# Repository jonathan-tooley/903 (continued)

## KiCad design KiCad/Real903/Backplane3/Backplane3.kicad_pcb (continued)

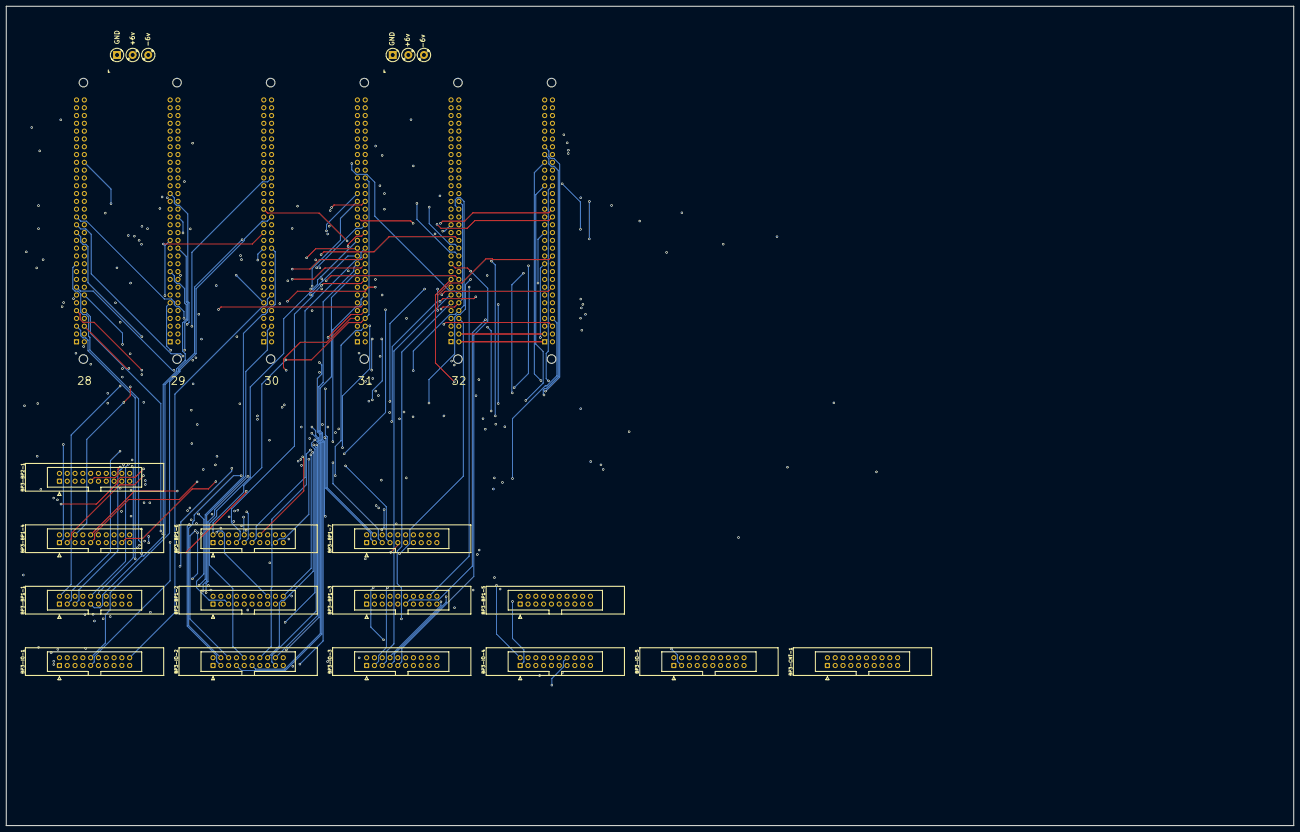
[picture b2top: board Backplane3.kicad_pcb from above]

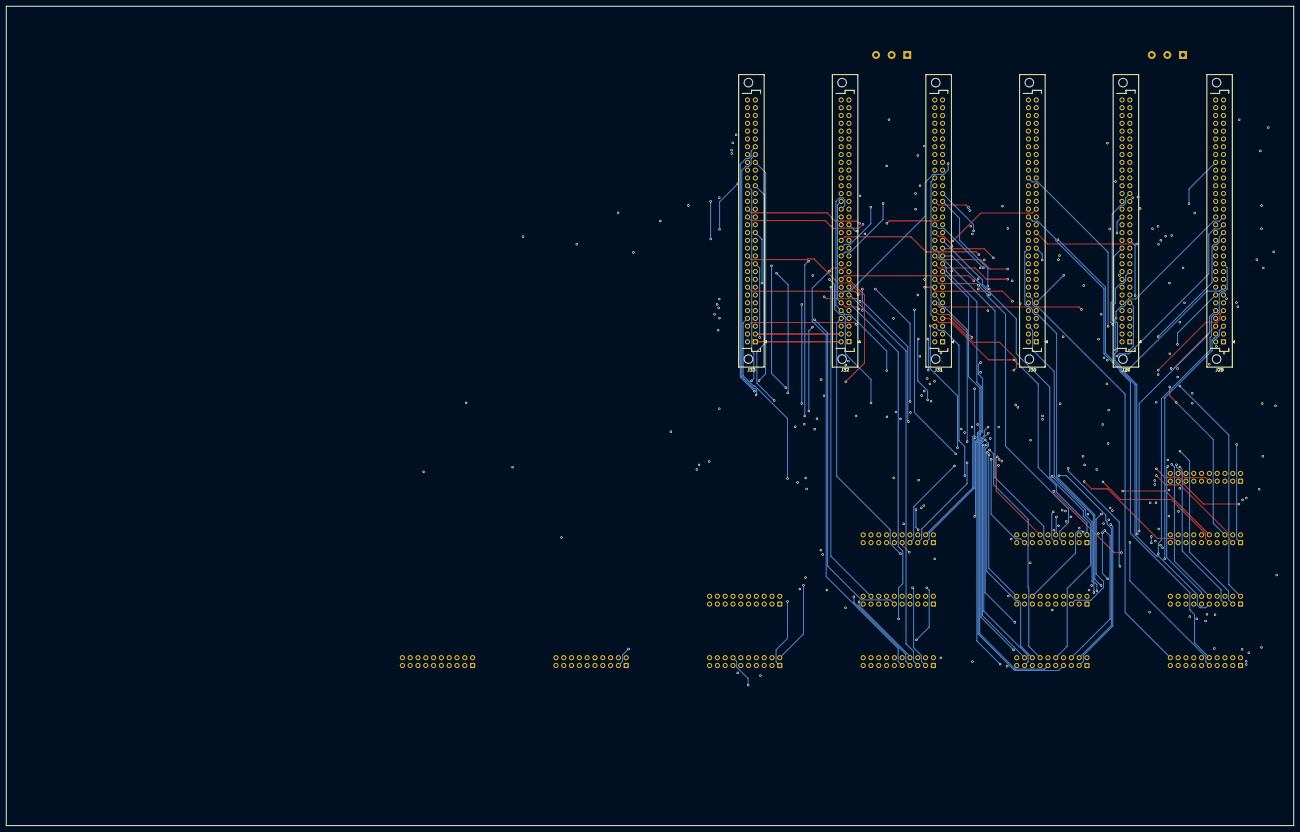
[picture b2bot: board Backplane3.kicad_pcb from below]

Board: 4 copper layers, 419.1 x 266.7 mm, 22 parts (6 on the bottom side), 236 nets.

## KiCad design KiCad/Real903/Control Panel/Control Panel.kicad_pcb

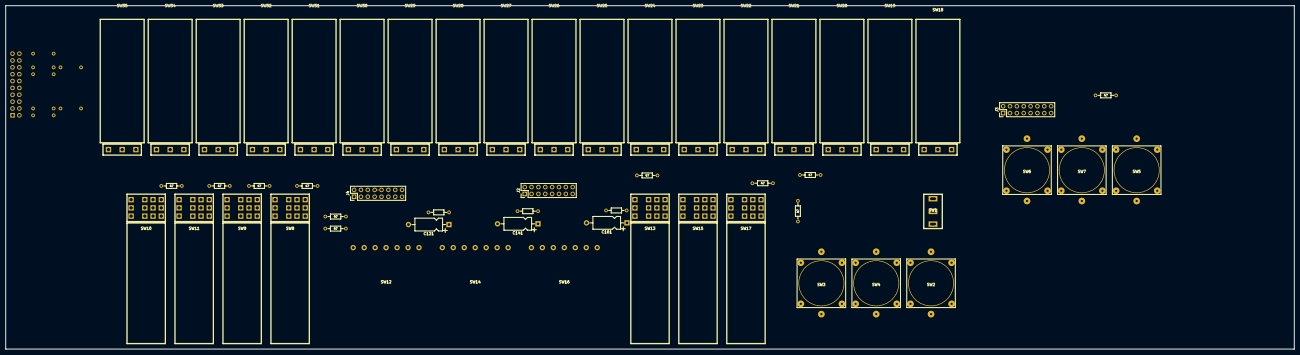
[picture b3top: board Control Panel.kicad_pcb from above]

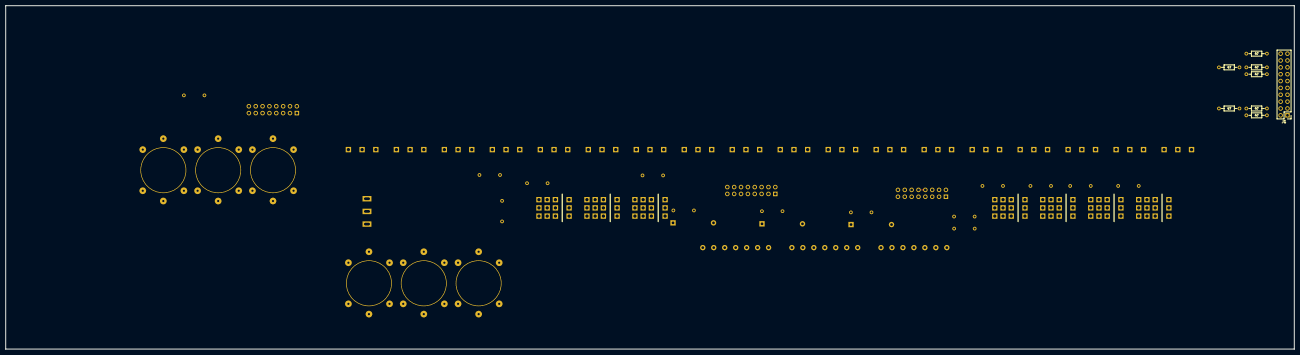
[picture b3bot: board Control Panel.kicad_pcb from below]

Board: 2 copper layers, 477.5 x 127.3 mm, 63 parts (8 on the bottom side), 92 nets.

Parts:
C121, C141, C161: CP_Axial_L10.0mm_D4.5mm_P15.00mm_Horizontal
J1: PinHeader_2x10_P2.54mm_Vertical
J2, J3, J4: PinHeader_2x08_P2.54mm_Vertical
R19, R20, R21, R24, R25, R29, R30, R31, R32, R33, R34, R35, R37, R38, R39, R40, R41, R42: 47; R_Axial_DIN0204_L3.6mm_D1.6mm_P7.62mm_Horizontal
R121, R141, R161: R_Axial_DIN0204_L3.6mm_D1.6mm_P7.62mm_Horizontal
SW1: MiniSPDTSwitch
SW2: Jump; EAO31
SW3: Stop; EAO31
SW4: Restart; EAO31
SW5: Reset; EAO31
SW6: On; EAO31
SW7: Off; EAO31
SW8: Obey; ElliottCPSwitch
SW9: Enter; ElliottCPSwitch
SW10: O/C Stop; ElliottCPSwitch
SW11: Cycle Repeat; ElliottCPSwitch
SW12: Int1; Honeywell Sw
SW13, SW15, SW17: Man/Trace; ElliottCPSwitch
SW14: Int2; Honeywell Sw
SW16: Int3; Honeywell Sw
SW18: NG1; ElliottNGSwitch
SW19: NG2; ElliottNGSwitch
SW20: NG3; ElliottNGSwitch
SW21: NG4; ElliottNGSwitch
SW22: NG5; ElliottNGSwitch
SW23: NG6; ElliottNGSwitch
SW24: NG7; ElliottNGSwitch
SW25: NG8; ElliottNGSwitch
SW26: NG9; ElliottNGSwitch
SW27: NG10; ElliottNGSwitch
SW28: NG11; ElliottNGSwitch
SW29: NG12; ElliottNGSwitch
SW30: NG13; ElliottNGSwitch
SW31: NG14; ElliottNGSwitch
SW32: NG15; ElliottNGSwitch
SW33: NG16; ElliottNGSwitch
SW34: NG17; ElliottNGSwitch
SW35: NG18; ElliottNGSwitch

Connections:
0v: J3.13, SW1.3, SW2.1, SW5.2, SW6.4, SW13.4, SW15.4, SW17.4
+6va: J3.16, R19.1, R20.1, R21.1, SW6.5, SW12.3, SW12.7, SW13.6, SW14.3, SW14.7, SW15.6, SW16.3, SW16.7, SW17.6
+6vb: J3.15, SW3.5, SW5.5, SW12.5, SW14.5, SW16.5
A: J3.8, SW1.2
CINS: J4.4, SW9.8
ENGk: J4.8, R42.1
INT1a: J2.14, SW13.5
INT1b: J2.16, R121.1
INT2a: J2.10, SW15.5
INT2b: J2.12, R141.1
INT3a: J2.6, SW17.5
INT3b: J2.8, R161.1
L: J3.14, SW7.5
M: J3.11, SW7.4
NG-1k: J3.1, SW18.1
NG-5k: J1.2, SW22.1
NG-6k: J1.3, SW23.1
NG-7k: J1.4, SW24.1
NG-8k: J1.5, SW25.1
NG-9k: J1.6, SW26.1
NG-10k: J1.7, SW27.1
NG-11k: J1.8, SW28.1
NG-12k: J1.9, SW29.1
NG-13k: J1.10, SW30.1
NG-17: J1.14, SW34.1
unnamed: C121.1, R121.2
unnamed: C121.2, SW12.2
unnamed: C141.1, R141.2
unnamed: C141.2, SW14.2
unnamed: C161.1, R161.2
unnamed: C161.2, SW16.2
unnamed: R19.2, SW13.1
unnamed: R20.2, SW15.1
unnamed: R21.2, SW17.1
unnamed: R24.2, SW3.3
unnamed: R25.2, SW5.1
unnamed: R29.2, SW35.3
unnamed: R30.2, SW33.3
unnamed: R31.2, SW32.3
unnamed: R32.2, SW31.3
unnamed: R33.2, SW21.3
unnamed: R34.2, SW20.3
unnamed: R35.2, SW19.3
unnamed: R37.2, SW8.4
unnamed: R38.2, SW8.3, SW8.6
unnamed: R39.2, SW10.3
unnamed: R40.2, SW11.3
unnamed: R41.2, SW9.3, SW9.6
unnamed: R42.2, SW9.4
unnamed: SW8.1, SW8.5
unnamed: SW8.7, SW9.7, SW9.12
unnamed: SW8.9, SW9.10
unnamed: SW9.1, SW9.5
unnamed: SW10.1, SW10.5
ONGk: J4.12, R37.1
ONOFFCommon: J3.7, SW7.2
Off: J3.9, SW6.2, SW7.1
On: J3.12, SW6.3
RESET: J3.6, SW5.4
RESETk: J3.4, R25.1
RSTk: J2.1, SW4.1
STOP: J2.5, SW3.4
{ACTIVE1}: J4.7, SW12.6
{ACTIVE2}: J4.3, SW14.6
{ACTIVE3}: J2.15, SW16.6
{INT1}: J4.5, SW12.4
{INT2}: J4.1, SW14.4
{INT3}: J2.13, SW16.4
~CINS: J4.2, SW9.11
~CSk: J4.15, SW10.6
~ENGk: J4.6, R41.1
~JUMP: J2.4, SW2.2
~NG-2k: J3.2, R35.1
~NG-3k: J3.3, R34.1
~NG-4k: J1.1, R33.1
~NG-14k: J1.11, R32.1
~NG-15k: J1.12, R31.1
~NG-16k: J1.13, R30.1
~NG-17: J1.15, SW34.3
~NG-18k: J1.16, R29.1
~ONGk: J4.10, R38.1
~OSk: J4.11, R39.1
~Operate: SW3.2, SW4.2, SW13.3, SW15.3, SW17.3, SW18.2, SW19.2, SW20.2, SW21.2, SW22.2, SW23.2, SW24.2, SW25.2, SW26.2, SW27.2, SW28.2, SW29.2, SW30.2
~PS1: J2.11, SW12.1, SW13.2
~PS2: J2.9, SW14.1, SW15.2
~PS3: J2.7, SW16.1, SW17.2
~RSTk: J2.2, SW4.3
~SMNk: J4.13, SW10.4
~STOPk: J2.3, R24.1
~TCSk: J4.9, R40.1
~TEST: SW8.2, SW8.8, SW9.2, SW10.2, SW11.2
~TestNoJump: J3.5, SW31.2, SW32.2, SW33.2, SW34.2, SW35.2

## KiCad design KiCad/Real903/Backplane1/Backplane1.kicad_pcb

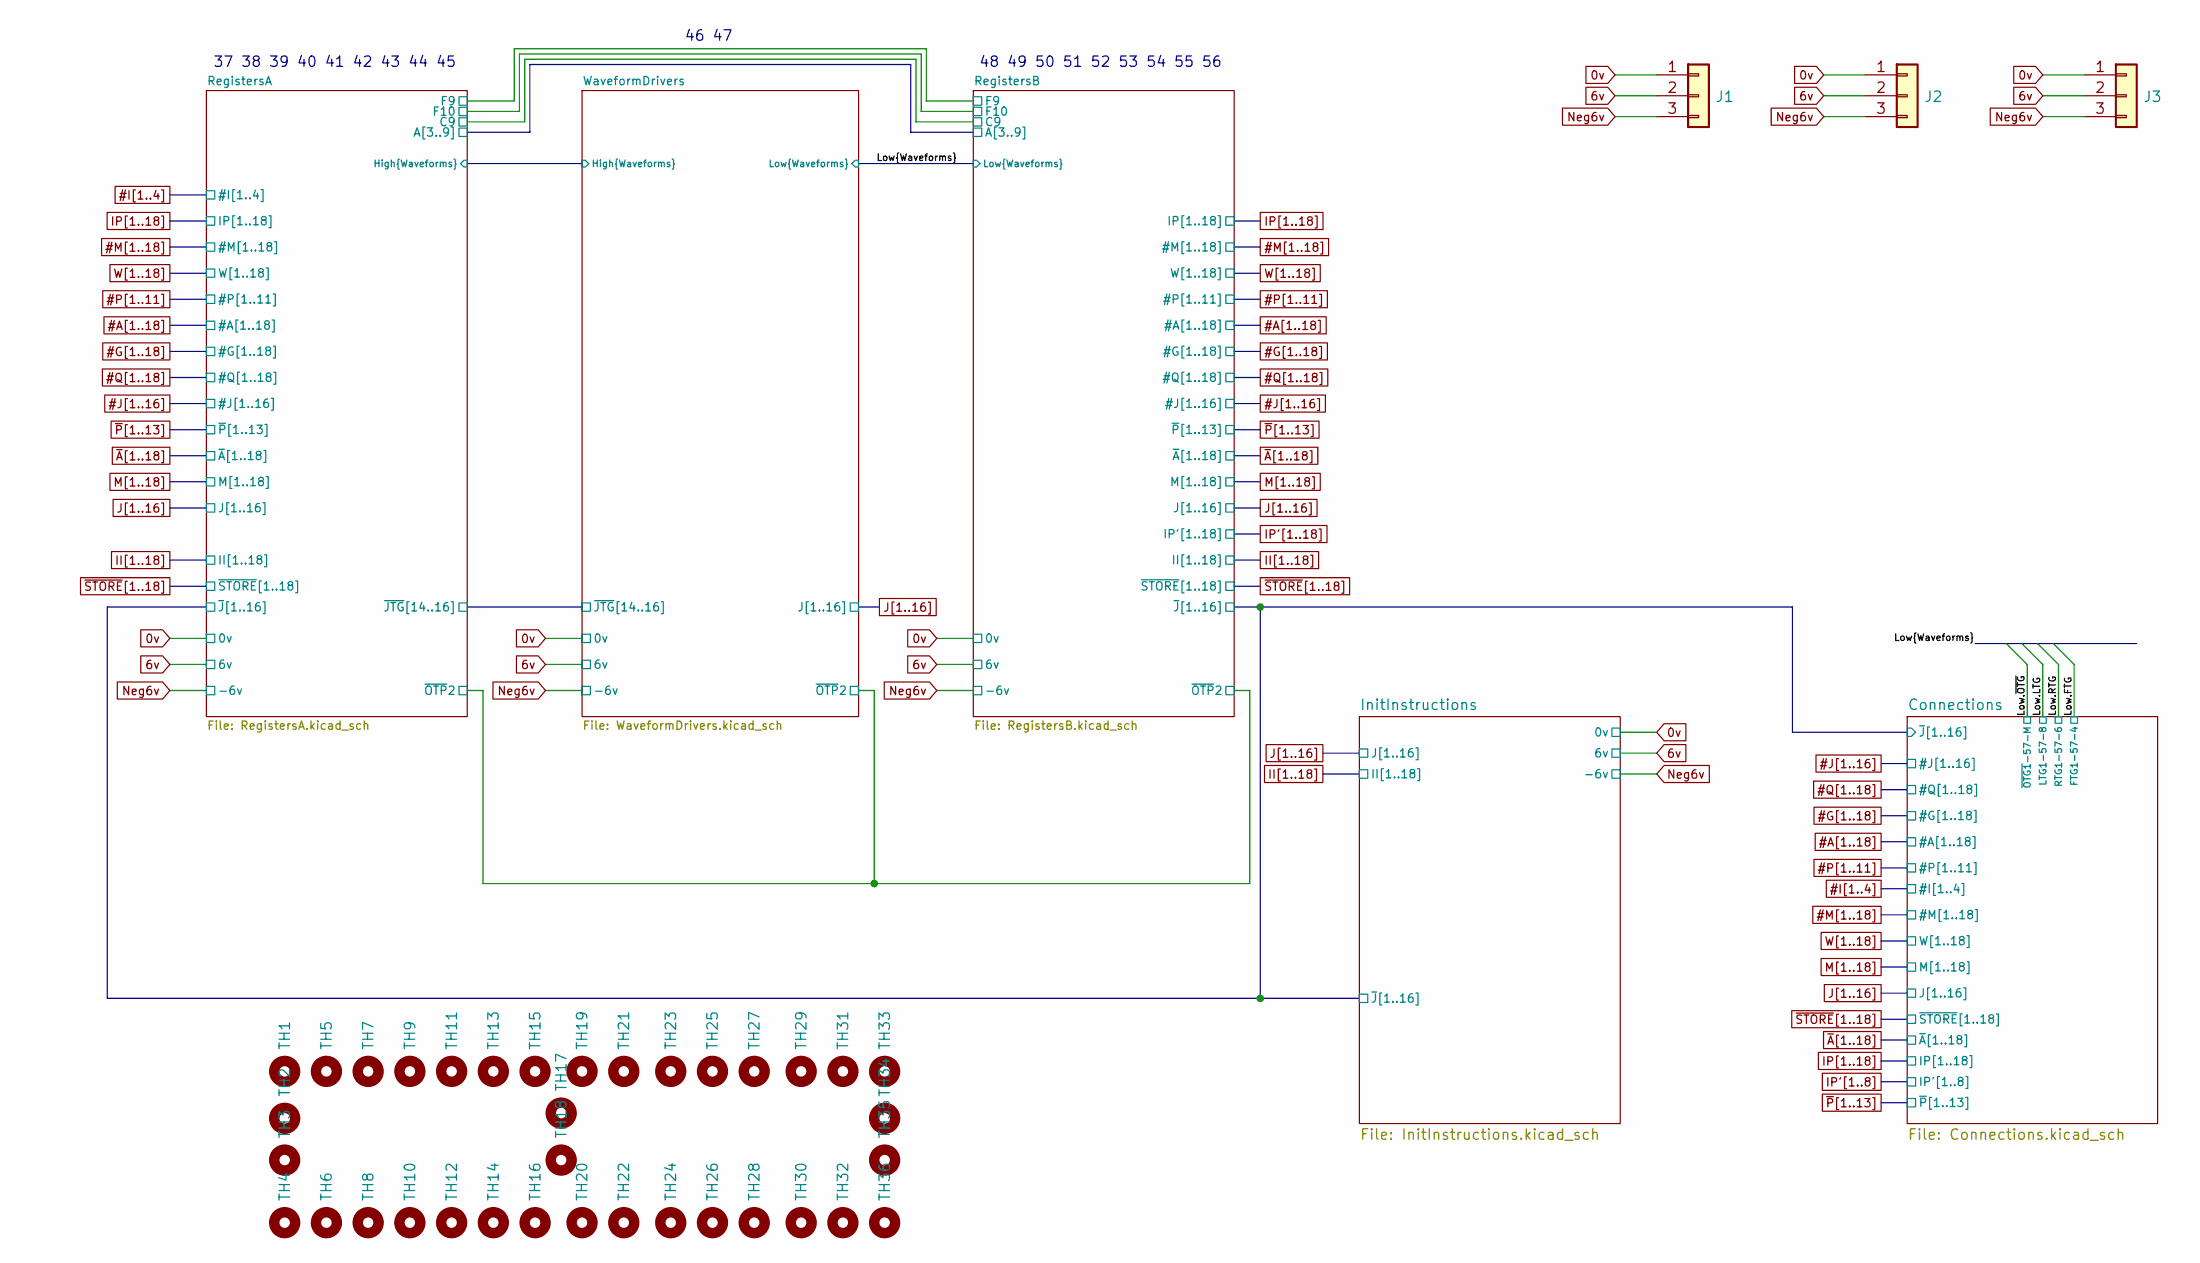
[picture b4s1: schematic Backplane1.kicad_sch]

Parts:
J1, J2, J3: TerminalBlock_5.08_1x03
TH1, TH2, TH3, TH4, TH5, TH6, TH7, TH8, TH9, TH10, TH11, TH12, TH13, TH14, TH15, TH16, TH17, TH18, TH19, TH20, TH21, TH22, TH23, TH24, TH25, TH26, TH27, TH28, TH29, TH30, TH31, TH32, TH33, TH34, TH35, TH36: MountingHole_2.7mm

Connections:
0v: J1.1, J2.1, J3.1; also elsewhere on the board
6v: J1.2, J2.2, J3.2; also elsewhere on the board
Neg6v: J1.3, J2.3, J3.3; also elsewhere on the board

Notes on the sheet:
48 49 50 51 52 53 54 55 56
37 38 39 40 41 42 43 44 45
46 47

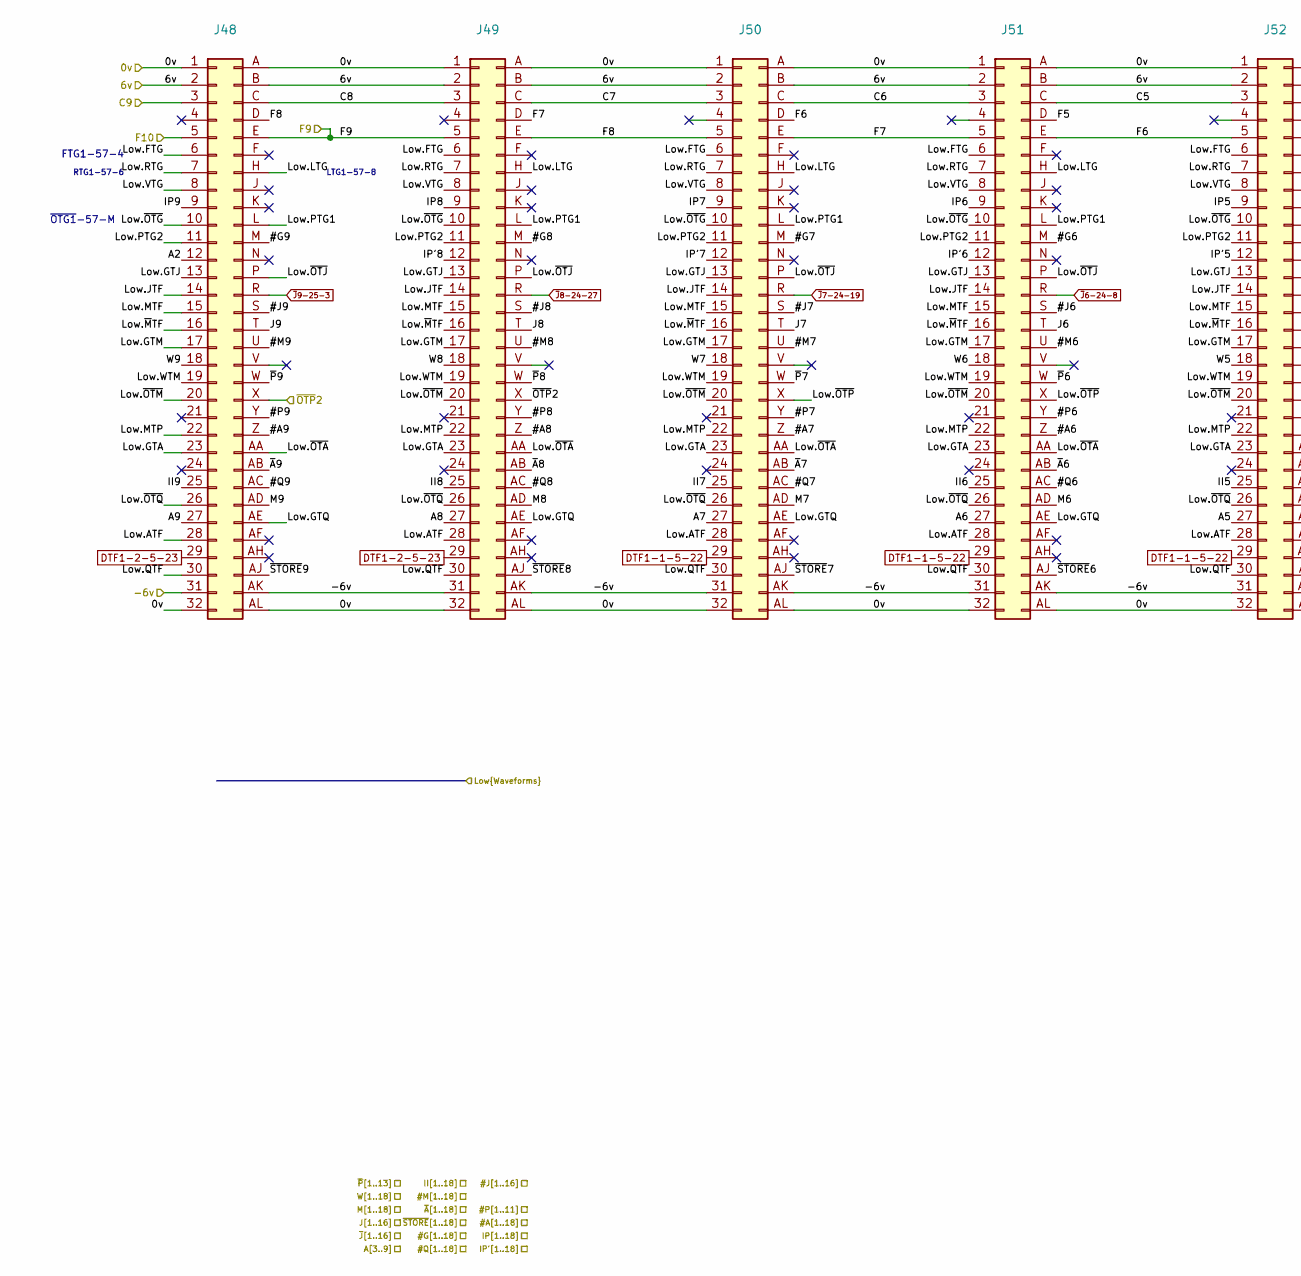
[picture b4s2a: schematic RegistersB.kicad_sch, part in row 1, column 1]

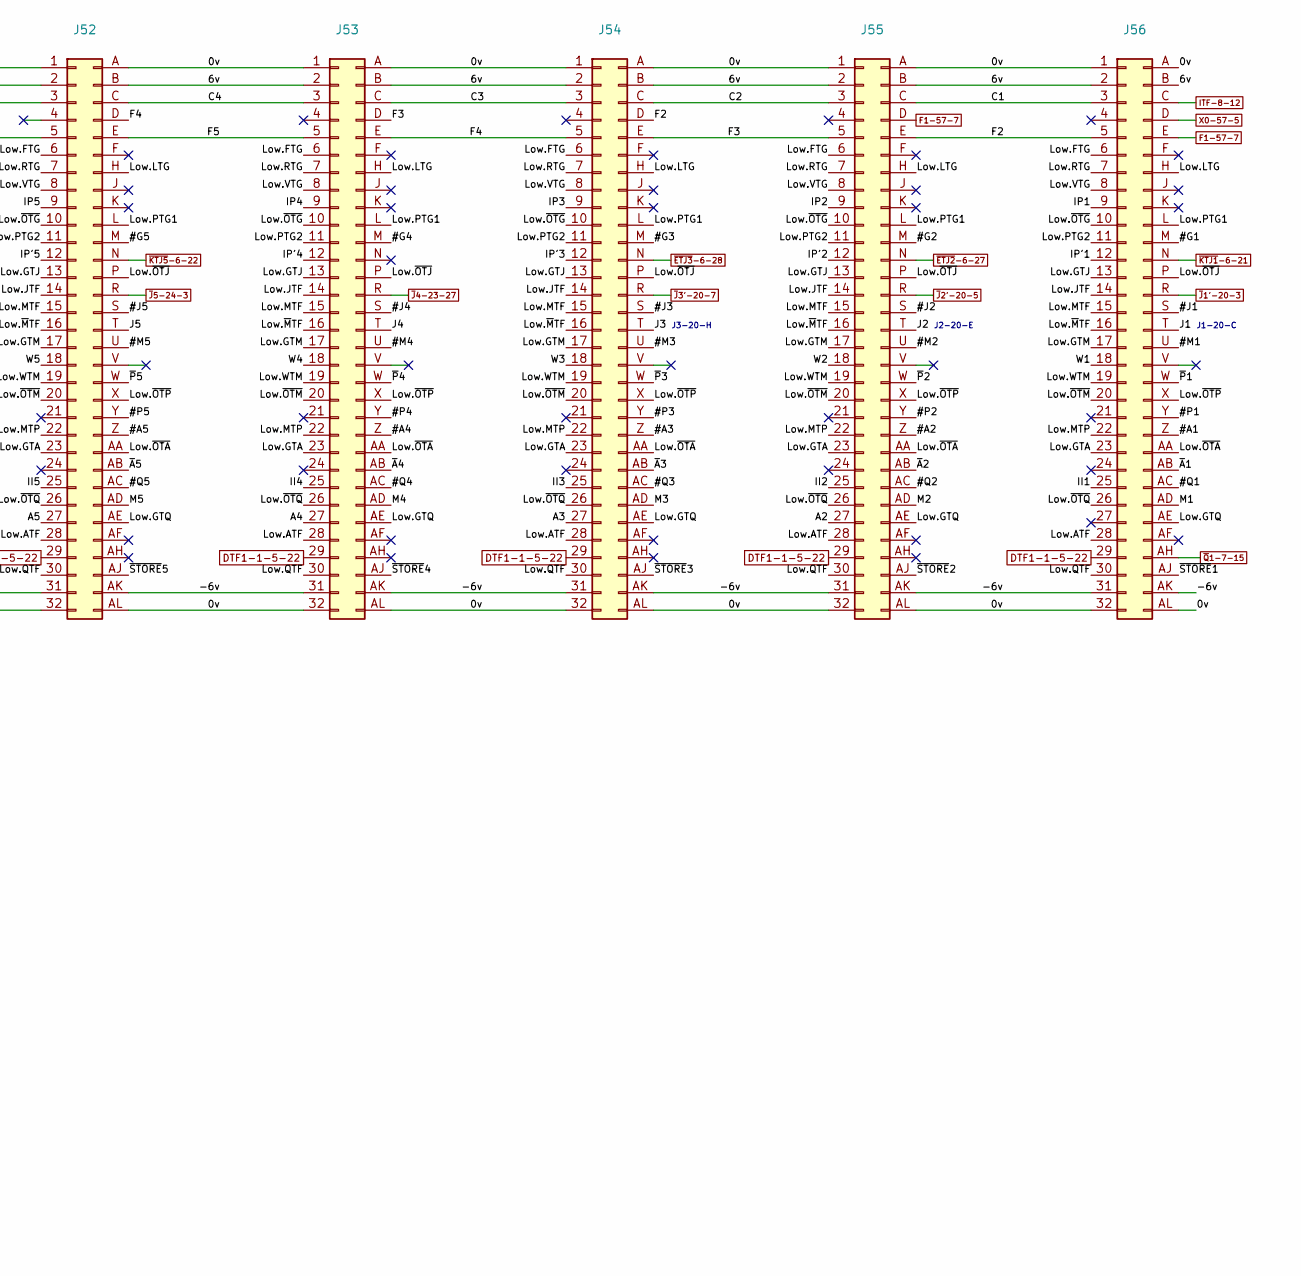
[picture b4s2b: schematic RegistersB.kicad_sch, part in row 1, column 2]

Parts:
J48, J49, J50, J51, J52, J53, J54, J55, J56: DIN41612_B_2x32_Vertical

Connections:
0v: J48.1, J48.32, J48.A, J48.AL, J49.1, J49.32, J49.A, J49.AL, J50.1, J50.32, J50.A, J50.AL, J51.1, J51.32, J51.A, J51.AL, J52.1, J52.32, J52.A, J52.AL, J53.1, J53.32, J53.A, J53.AL, J54.1, J54.32, J54.A, J54.AL, J55.1, J55.32, J55.A, J55.AL, J56.1, J56.32, J56.A, J56.AL; also elsewhere on the board
6v: J48.2, J48.B, J49.2, J49.B, J50.2, J50.B, J51.2, J51.B, J52.2, J52.B, J53.2, J53.B, J54.2, J54.B, J55.2, J55.B, J56.2, J56.B; also elsewhere on the board
#A1: J56.Z; also elsewhere on the board
#A2: J55.Z; also elsewhere on the board
#A3: J54.Z; also elsewhere on the board
#A4: J53.Z; also elsewhere on the board
#A5: J52.Z; also elsewhere on the board
#A6: J51.Z; also elsewhere on the board
#A7: J50.Z; also elsewhere on the board
#A8: J49.Z; also elsewhere on the board
#A9: J48.Z; also elsewhere on the board
#G1: J56.M; also elsewhere on the board
#G2: J55.M; also elsewhere on the board
#G3: J54.M; also elsewhere on the board
#G4: J53.M; also elsewhere on the board
#G5: J52.M; also elsewhere on the board
#G6: J51.M; also elsewhere on the board
#G7: J50.M; also elsewhere on the board
#G8: J49.M; also elsewhere on the board
#G9: J48.M; also elsewhere on the board
#J1: J56.S; also elsewhere on the board
#J2: J55.S; also elsewhere on the board
#J3: J54.S; also elsewhere on the board
#J4: J53.S; also elsewhere on the board
#J5: J52.S; also elsewhere on the board
#J6: J51.S; also elsewhere on the board
#J7: J50.S; also elsewhere on the board
#J8: J49.S; also elsewhere on the board
#J9: J48.S; also elsewhere on the board
#M1: J56.U; also elsewhere on the board
#M2: J55.U; also elsewhere on the board
#M3: J54.U; also elsewhere on the board
#M4: J53.U; also elsewhere on the board
#M5: J52.U; also elsewhere on the board
#M6: J51.U; also elsewhere on the board
#M7: J50.U; also elsewhere on the board
#M8: J49.U; also elsewhere on the board
#M9: J48.U; also elsewhere on the board
#P1: J56.Y; also elsewhere on the board
#P2: J55.Y; also elsewhere on the board
#P3: J54.Y; also elsewhere on the board
#P4: J53.Y; also elsewhere on the board
#P5: J52.Y; also elsewhere on the board
#P6: J51.Y; also elsewhere on the board
#P7: J50.Y; also elsewhere on the board
#P8: J49.Y; also elsewhere on the board
#P9: J48.Y; also elsewhere on the board
#Q1: J56.AC; also elsewhere on the board
#Q2: J55.AC; also elsewhere on the board
#Q3: J54.AC; also elsewhere on the board
#Q4: J53.AC; also elsewhere on the board
#Q5: J52.AC; also elsewhere on the board
#Q6: J51.AC; also elsewhere on the board
#Q7: J50.AC; also elsewhere on the board
#Q8: J49.AC; also elsewhere on the board
#Q9: J48.AC; also elsewhere on the board
/Low.FTG: J48.6, J49.6, J50.6, J51.6, J52.6, J53.6, J54.6, J55.6, J56.6; also elsewhere on the board
/Low.GTA: J48.23, J49.23, J50.23, J51.23, J52.23, J53.23, J54.23, J55.23, J56.23; also elsewhere on the board
/Low.GTJ: J48.13, J49.13, J50.13, J51.13, J52.13, J53.13, J54.13, J55.13, J56.13; also elsewhere on the board
/Low.GTM: J48.17, J49.17, J50.17, J51.17, J52.17, J53.17, J54.17, J55.17, J56.17; also elsewhere on the board
/Low.JTF: J48.14, J49.14, J50.14, J51.14, J52.14, J53.14, J54.14, J55.14, J56.14; also elsewhere on the board
/Low.LTG: J48.H, J49.H, J50.H, J51.H, J52.H, J53.H, J54.H, J55.H, J56.H; also elsewhere on the board
/Low.MTF: J48.15, J49.15, J50.15, J51.15, J52.15, J53.15, J54.15, J55.15, J56.15; also elsewhere on the board
/Low.MTP: J48.22, J49.22, J50.22, J51.22, J52.22, J53.22, J54.22, J55.22, J56.22; also elsewhere on the board
/Low.PTG1: J48.L, J49.L, J50.L, J51.L, J52.L, J53.L, J54.L, J55.L, J56.L; also elsewhere on the board
/Low.PTG2: J48.11, J49.11, J50.11, J51.11, J52.11, J53.11, J54.11, J55.11, J56.11; also elsewhere on the board
/Low.RTG: J48.7, J49.7, J50.7, J51.7, J52.7, J53.7, J54.7, J55.7, J56.7; also elsewhere on the board
/Low.VTG: J48.8, J49.8, J50.8, J51.8, J52.8, J53.8, J54.8, J55.8, J56.8; also elsewhere on the board
/Low.WTM: J48.19, J49.19, J50.19, J51.19, J52.19, J53.19, J54.19, J55.19, J56.19; also elsewhere on the board
/Low.~OTG: J48.10, J49.10, J50.10, J51.10, J52.10, J53.10, J54.10, J55.10, J56.10; also elsewhere on the board
/Low.~OTJ: J48.P, J49.P, J50.P, J51.P, J52.P, J53.P, J54.P, J55.P, J56.P; also elsewhere on the board
/Low.~OTM: J48.20, J49.20, J50.20, J51.20, J52.20, J53.20, J54.20, J55.20, J56.20; also elsewhere on the board
/RegistersA/A3: J54.27; also elsewhere on the board
/RegistersA/A4: J53.27; also elsewhere on the board
/RegistersA/A5: J52.27; also elsewhere on the board
/RegistersA/A6: J51.27; also elsewhere on the board
/RegistersA/A7: J50.27; also elsewhere on the board
/RegistersA/A8: J49.27; also elsewhere on the board
/RegistersA/A9: J48.27; also elsewhere on the board
/RegistersA/C9: J48.3; also elsewhere on the board
/RegistersA/F10: J48.5; also elsewhere on the board
/RegistersA/~OTP2: J48.X, J49.X; also elsewhere on the board
/RegistersB/A2: J48.12, J55.27
/RegistersB/ATF1: J48.28, J49.28, J50.28, J51.28, J52.28, J53.28, J54.28, J55.28, J56.28; also elsewhere on the board
/RegistersB/C1: J55.C, J56.3
/RegistersB/C2: J54.C, J55.3
/RegistersB/C3: J53.C, J54.3
/RegistersB/C4: J52.C, J53.3
/RegistersB/C5: J51.C, J52.3
/RegistersB/C6: J50.C, J51.3
/RegistersB/C7: J49.C, J50.3
/RegistersB/C8: J48.C, J49.3
/RegistersB/F2: J54.D, J55.E, J56.5
/RegistersB/F3: J53.D, J54.E, J55.5
/RegistersB/F4: J52.D, J53.E, J54.5
/RegistersB/F5: J51.D, J52.E, J53.5
/RegistersB/F6: J50.D, J51.E, J52.5
/RegistersB/F7: J49.D, J50.E, J51.5
/RegistersB/F8: J48.D, J49.E, J50.5
/RegistersB/F9: J48.E, J49.5; also elsewhere on the board
/RegistersB/GTQ1: J48.AE, J49.AE, J50.AE, J51.AE, J52.AE, J53.AE, J54.AE, J55.AE, J56.AE; also elsewhere on the board
/RegistersB/QTF1: J48.30, J49.30, J50.30, J51.30, J52.30, J53.30, J54.30, J55.30, J56.30; also elsewhere on the board
/RegistersB/~MTF1: J48.16, J49.16, J50.16, J51.16, J52.16, J53.16, J54.16, J55.16, J56.16; also elsewhere on the board
/RegistersB/~OTA1: J48.AA, J49.AA, J50.AA, J51.AA, J52.AA, J53.AA, J54.AA, J55.AA, J56.AA; also elsewhere on the board
/RegistersB/~OTP1: J50.X, J51.X, J52.X, J53.X, J54.X, J55.X, J56.X; also elsewhere on the board
/RegistersB/~OTQ1: J48.26, J49.26, J50.26, J51.26, J52.26, J53.26, J54.26, J55.26, J56.26; also elsewhere on the board
DTF1-1-5-22: J50.29, J51.29, J52.29, J53.29, J54.29, J55.29, J56.29; also elsewhere on the board
DTF1-2-5-23: J48.29, J49.29; also elsewhere on the board
F1-57-7: J55.D, J56.E; also elsewhere on the board
II1: J56.25; also elsewhere on the board
II2: J55.25; also elsewhere on the board
II3: J54.25; also elsewhere on the board
II4: J53.25; also elsewhere on the board
II5: J52.25; also elsewhere on the board
II6: J51.25; also elsewhere on the board
II7: J50.25; also elsewhere on the board
II8: J49.25; also elsewhere on the board
II9: J48.25; also elsewhere on the board
IP1: J56.9; also elsewhere on the board
IP2: J55.9; also elsewhere on the board
IP3: J54.9; also elsewhere on the board
IP4: J53.9; also elsewhere on the board
IP5: J52.9; also elsewhere on the board
IP6: J51.9; also elsewhere on the board
IP7: J50.9; also elsewhere on the board
IP8: J49.9; also elsewhere on the board
IP9: J48.9; also elsewhere on the board
IP'1: J56.12; also elsewhere on the board
IP'2: J55.12; also elsewhere on the board
IP'3: J54.12; also elsewhere on the board
IP'4: J53.12; also elsewhere on the board
IP'5: J52.12; also elsewhere on the board
IP'6: J51.12; also elsewhere on the board
IP'7: J50.12; also elsewhere on the board
IP'8: J49.12; also elsewhere on the board
ITF-8-12: J56.C; also elsewhere on the board
J1: J56.T; also elsewhere on the board
J2: J55.T; also elsewhere on the board
J3: J54.T; also elsewhere on the board
J4: J53.T; also elsewhere on the board
J5: J52.T; also elsewhere on the board
J6: J51.T; also elsewhere on the board
J7: J50.T; also elsewhere on the board
J8: J49.T; also elsewhere on the board
J9: J48.T; also elsewhere on the board
M1: J56.AD; also elsewhere on the board
M2: J55.AD; also elsewhere on the board
M3: J54.AD; also elsewhere on the board
M4: J53.AD; also elsewhere on the board
M5: J52.AD; also elsewhere on the board
M6: J51.AD; also elsewhere on the board
M7: J50.AD; also elsewhere on the board
M8: J49.AD; also elsewhere on the board
M9: J48.AD; also elsewhere on the board
Neg6v: J48.31, J48.AK, J49.31, J49.AK, J50.31, J50.AK, J51.31, J51.AK, J52.31, J52.AK, J53.31, J53.AK, J54.31, J54.AK, J55.31, J55.AK, J56.31, J56.AK; also elsewhere on the board
W1: J56.18; also elsewhere on the board
W2: J55.18; also elsewhere on the board
W3: J54.18; also elsewhere on the board
W4: J53.18; also elsewhere on the board
W5: J52.18; also elsewhere on the board
W6: J51.18; also elsewhere on the board
W7: J50.18; also elsewhere on the board
W8: J49.18; also elsewhere on the board
W9: J48.18; also elsewhere on the board
X0-57-5: J56.D; also elsewhere on the board
~A1: J56.AB; also elsewhere on the board
~A2: J55.AB; also elsewhere on the board
~A3: J54.AB; also elsewhere on the board
~A4: J53.AB; also elsewhere on the board
~A5: J52.AB; also elsewhere on the board
~A6: J51.AB; also elsewhere on the board
~A7: J50.AB; also elsewhere on the board
~A8: J49.AB; also elsewhere on the board
~A9: J48.AB; also elsewhere on the board
~ETJ2-6-27: J55.N; also elsewhere on the board
~ETJ3-6-28: J54.N; also elsewhere on the board
~J1'-20-3: J56.R; also elsewhere on the board
~J2'-20-5: J55.R; also elsewhere on the board
~J3'-20-7: J54.R; also elsewhere on the board
~J4-23-27: J53.R; also elsewhere on the board
~J5-24-3: J52.R; also elsewhere on the board
~J6-24-8: J51.R; also elsewhere on the board
~J7-24-19: J50.R; also elsewhere on the board
~J8-24-27: J49.R; also elsewhere on the board
~J9-25-3: J48.R; also elsewhere on the board
~KTJ1-6-21: J56.N; also elsewhere on the board
~KTJ5-6-22: J52.N; also elsewhere on the board
~P1: J56.W; also elsewhere on the board
~P2: J55.W; also elsewhere on the board
~P3: J54.W; also elsewhere on the board
~P4: J53.W; also elsewhere on the board
~P5: J52.W; also elsewhere on the board
~P6: J51.W; also elsewhere on the board
~P7: J50.W; also elsewhere on the board
~P8: J49.W; also elsewhere on the board
~P9: J48.W; also elsewhere on the board
~Q1-7-15: J56.AH; also elsewhere on the board
~STORE1: J56.AJ; also elsewhere on the board
~STORE2: J55.AJ; also elsewhere on the board
~STORE3: J54.AJ; also elsewhere on the board
~STORE4: J53.AJ; also elsewhere on the board
~STORE5: J52.AJ; also elsewhere on the board
~STORE6: J51.AJ; also elsewhere on the board
~STORE7: J50.AJ; also elsewhere on the board
~STORE8: J49.AJ; also elsewhere on the board
~STORE9: J48.AJ; also elsewhere on the board

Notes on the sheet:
~{OTG1}-57-M
J1-20-C
FTG1-57-4
RTG1-57-6
J3-20-H
LTG1-57-8
J2-20-E
